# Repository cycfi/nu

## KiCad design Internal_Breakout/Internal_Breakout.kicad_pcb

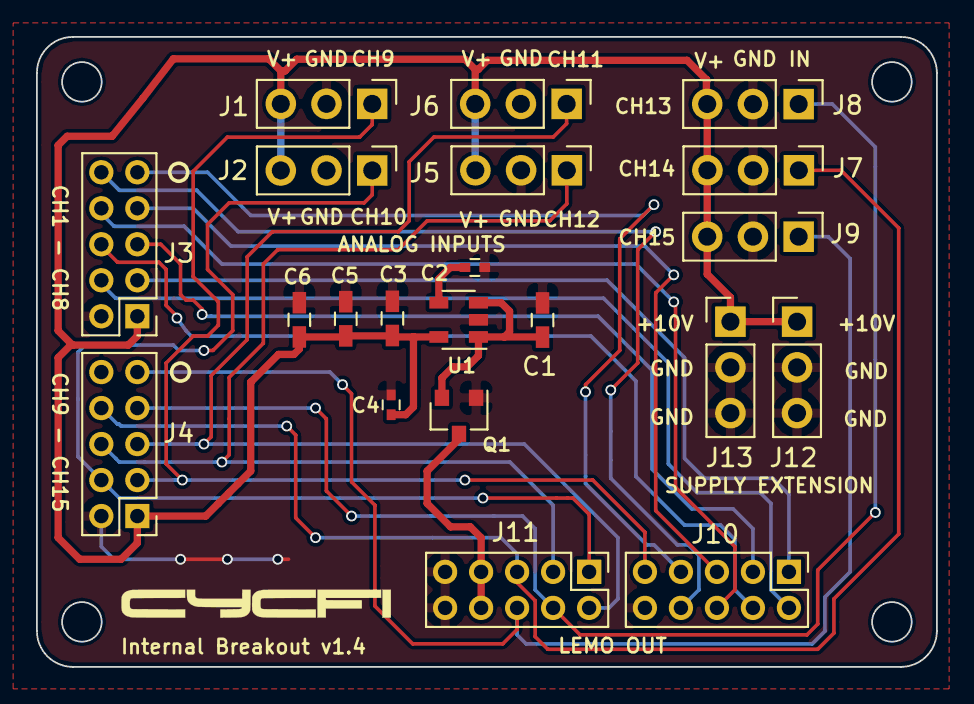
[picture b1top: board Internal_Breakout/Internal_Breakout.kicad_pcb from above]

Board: 2 copper layers, 50.0 x 35.0 mm, 21 parts (0 on the bottom side), 20 nets.

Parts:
C1, C5: 1uF; C_0603_HandSoldering
C2: 10nF; C_0402
C3: 2.2uF; C_0603_HandSoldering
C4: 1nF; C_0402
C6: 10uF; C_0603_HandSoldering
J1, J2, J5, J6, J7, J8, J9, J12, J13: CONN_01X03; Pin_Header_Straight_1x03_Pitch2.54mm
J3, J4, J10, J11: CONN_01X10; Pin_Header_Straight_2x05_Pitch2.00mm
Q1: DMP3099L-7; SOT-23
U1: LP2985-10DVBR; SOT-23-5

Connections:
+10VA: C3.1, C4.1, C5.1, C6.1, J1.3, J2.3, J3.1, J4.1, J5.3, J6.3, J7.3, J8.3, J9.3, J12.1, J13.1, U1.5
+VDC_IN: J11.7, J11.8, Q1.3
CH1: J3.3, J10.1
CH2: J3.4, J10.2
CH3: J3.5, J10.3
CH4: J3.6, J10.4
CH5: J3.7, J10.5
CH6: J3.8, J10.6
CH7: J3.9, J10.7
CH8: J3.10, J10.8
CH9: J1.1, J4.3, J10.9
CH10: J2.1, J4.4, J11.1
CH11: J4.5, J6.1, J11.2
CH12: J4.6, J5.1, J11.3
CH13: J4.7, J8.1, J11.4
CH14: J4.8, J7.1, J11.5
CH15: J4.9, J9.1, J11.6
GND: C1.2, C2.2, C3.2, C4.2, C5.2, C6.2, J1.2, J2.2, J3.2, J4.2, J5.2, J6.2, J7.2, J8.2, J9.2, J10.10, J11.9, J11.10, J12.2, J12.3, J13.2, J13.3, Q1.1, U1.2
unnamed: C1.1, Q1.2, U1.1, U1.3
unnamed: C2.1, U1.4

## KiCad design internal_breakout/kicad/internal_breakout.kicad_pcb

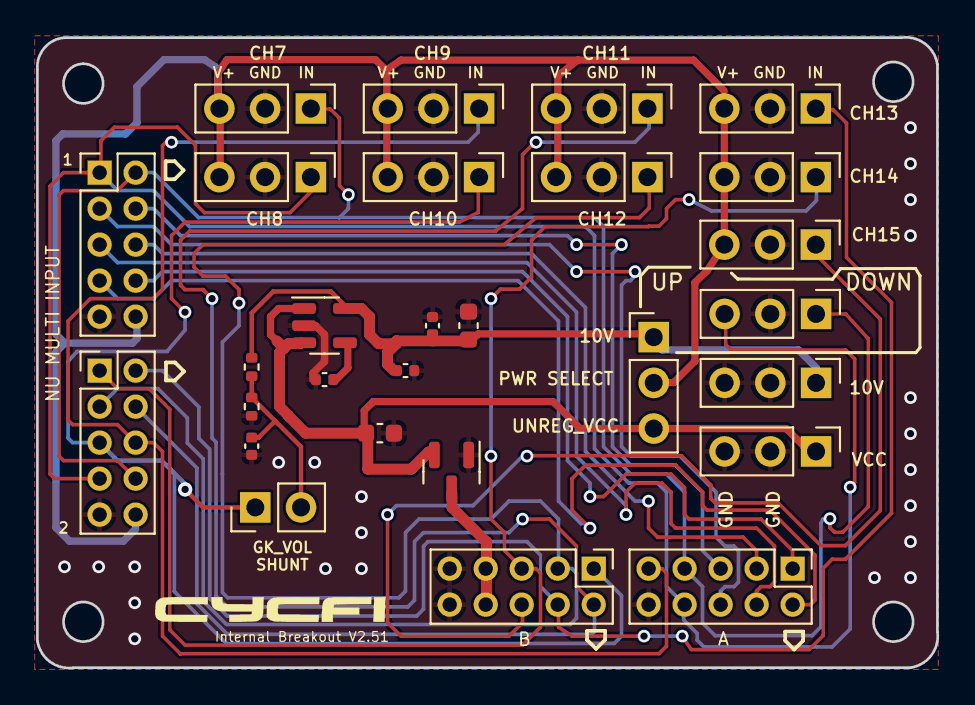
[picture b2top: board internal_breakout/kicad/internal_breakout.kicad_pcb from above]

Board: 2 copper layers, 50.0 x 35.0 mm, 28 parts (0 on the bottom side), 22 nets.

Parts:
C1, C2: 10uF; C_0603_1608Metric
C3, C6: 1uF; C_0402_1005Metric
C4: 10nF; C_0402_1005Metric
C5: 100nF; C_0402_1005Metric
J1, J2, J5, J6, J7, J8, J9, J12, J13, J14: MA03-1; PinHeader_1x03_P2.54mm_Vertical
J3, J4, J10, J11: 2X5; PinHeader_2x05_P2.00mm_Vertical
J15, J16, J17: Conn_01x03; PinHeader_1x03_P2.54mm_Vertical
J18: Conn_02x01; PinHeader_1x02_P2.54mm_Vertical
Q1: DMP3099L-7; SOT-23
R1, R2: 47K; R_0402_1005Metric
U1: LP2985-10DBVR; SOT-23-5

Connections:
+10VA: C2.1, C3.1, C5.1, J12.1, J14.1, R1.1, U1.5 (VOUT)
CH1: J3.8, J10.1
CH2: J3.7, J10.2
CH3: J3.6, J10.3
CH4: J3.5, J10.4
CH5: J3.4, J10.5
CH6: J3.3, J10.6
CH7: J3.2, J4.8, J10.7, J15.1, J17.1
CH8: J3.1, J4.7, J10.8, J16.1, J17.3
CH9: J1.1, J4.6, J10.9
CH10: J2.1, J4.5, J11.1, J18.1
CH11: J4.4, J6.1, J11.2
CH12: J4.3, J5.1, J11.3
CH13: J4.2, J8.1, J11.4
CH14: J4.1, J7.1, J11.5
CH15: J9.1, J11.6
GND: C1.2, C2.2, C3.2, C4.2, C5.2, C6.2, J1.2, J2.2, J3.9, J4.9, J5.2, J6.2, J7.2, J8.2, J9.2, J10.10, J11.9, J11.10, J12.2, J12.3, J13.2, J13.3, J15.2, J16.2, J17.2, Q1.1 (G), R2.2, U1.2 (GND)
unnamed: C4.1, U1.4 (BYPASS)
unnamed: C6.1, J18.2, R1.2, R2.1
V+: J1.3, J2.3, J3.10, J4.10, J5.3, J6.3, J7.3, J8.3, J9.3, J14.2, J15.3, J16.3
VCC: C1.1, J13.1, J14.3, Q1.2 (S), U1.1 (VIN), U1.3 (ON/OFF)
VIN: J11.7, J11.8, Q1.3 (D)

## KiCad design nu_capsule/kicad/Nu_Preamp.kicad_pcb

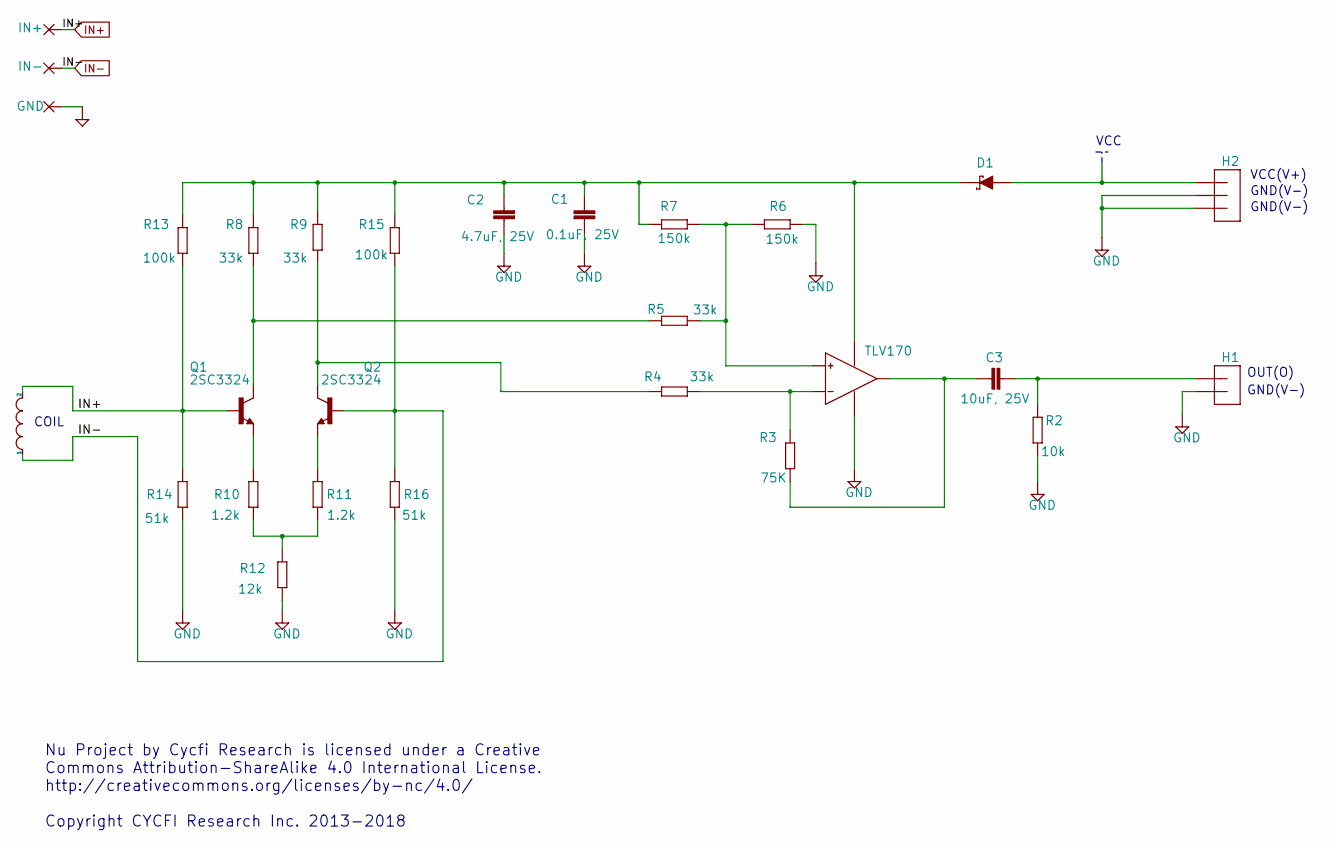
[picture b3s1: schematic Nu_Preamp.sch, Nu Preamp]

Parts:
C1: 0.1uF, 25V; C0402
C2: 4.7uF, 25V; C0603_NK
C3: 10uF, 25V; C0603_NK
D1: SOD323
GND: SMD1_27-2_54
H1: 2P-2MM-TH-MALE; 2P-2MM-TH
H2: 3P-2MM-TH-MALE; 3P-2MM-TH
IN+: SMD1_27-2_54
IN-: SMD1_27-2_54
Q1, Q2: 2SC3324; SOT23
R2: 10k; R0402
R3: 75K; R0402
R4, R5, R8, R9: 33k; R0402
R6, R7: 150k; R0402
R10, R11: 1.2k; R0402
R12: 12k; R0402
R13, R15: 100k; R0402
R14, R16: 51k; R0402
U1: TLV170; SOT23-5

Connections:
GND: C1.2, C2.1, GND.1, H1.P$2 (2), H2.P$2 (2), H2.P$3 (3), R2.1, R6.1, R12.1, R14.1, R16.1, U1.2
IN+: IN+.1, Q1.1 (B), R13.1, R14.2
IN-: IN-.1, Q2.1 (B), R15.1, R16.2
unnamed: C3.2, H1.P$1 (1), R2.2
unnamed: Q1.3 (C), R5.2, R8.1
unnamed: Q2.3 (C), R4.2, R9.1
unnamed: Q1.2 (E), R10.2
unnamed: Q2.2 (E), R11.2
unnamed: R10.1, R11.1, R12.2
unnamed: R5.1, R6.2, R7.1, U1.3
unnamed: R3.1, R4.1, U1.4
unnamed: C3.1, R3.2, U1.1
unnamed: D1.1 (A), H2.P$1 (1)
VCC1: C1.1, C2.2, D1.2 (C), R7.2, R8.2, R9.2, R13.2, R15.2, U1.5

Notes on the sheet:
Nu Project by Cycfi Research is licensed under a Creative Commons Attribution-ShareAlike 4.0 International License. http://creativecommons.org/licenses/by-nc/4.0/ Copyright CYCFI Research Inc. 2013-2018
VCC
COIL
VCC(V+)
GND(V-)
OUT(O)

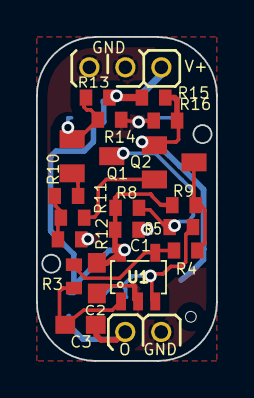
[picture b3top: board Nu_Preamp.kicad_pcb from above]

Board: 2 copper layers, 10.0 x 18.0 mm, 28 parts (0 on the bottom side), 14 nets.

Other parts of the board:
@HOLE0: (no value)

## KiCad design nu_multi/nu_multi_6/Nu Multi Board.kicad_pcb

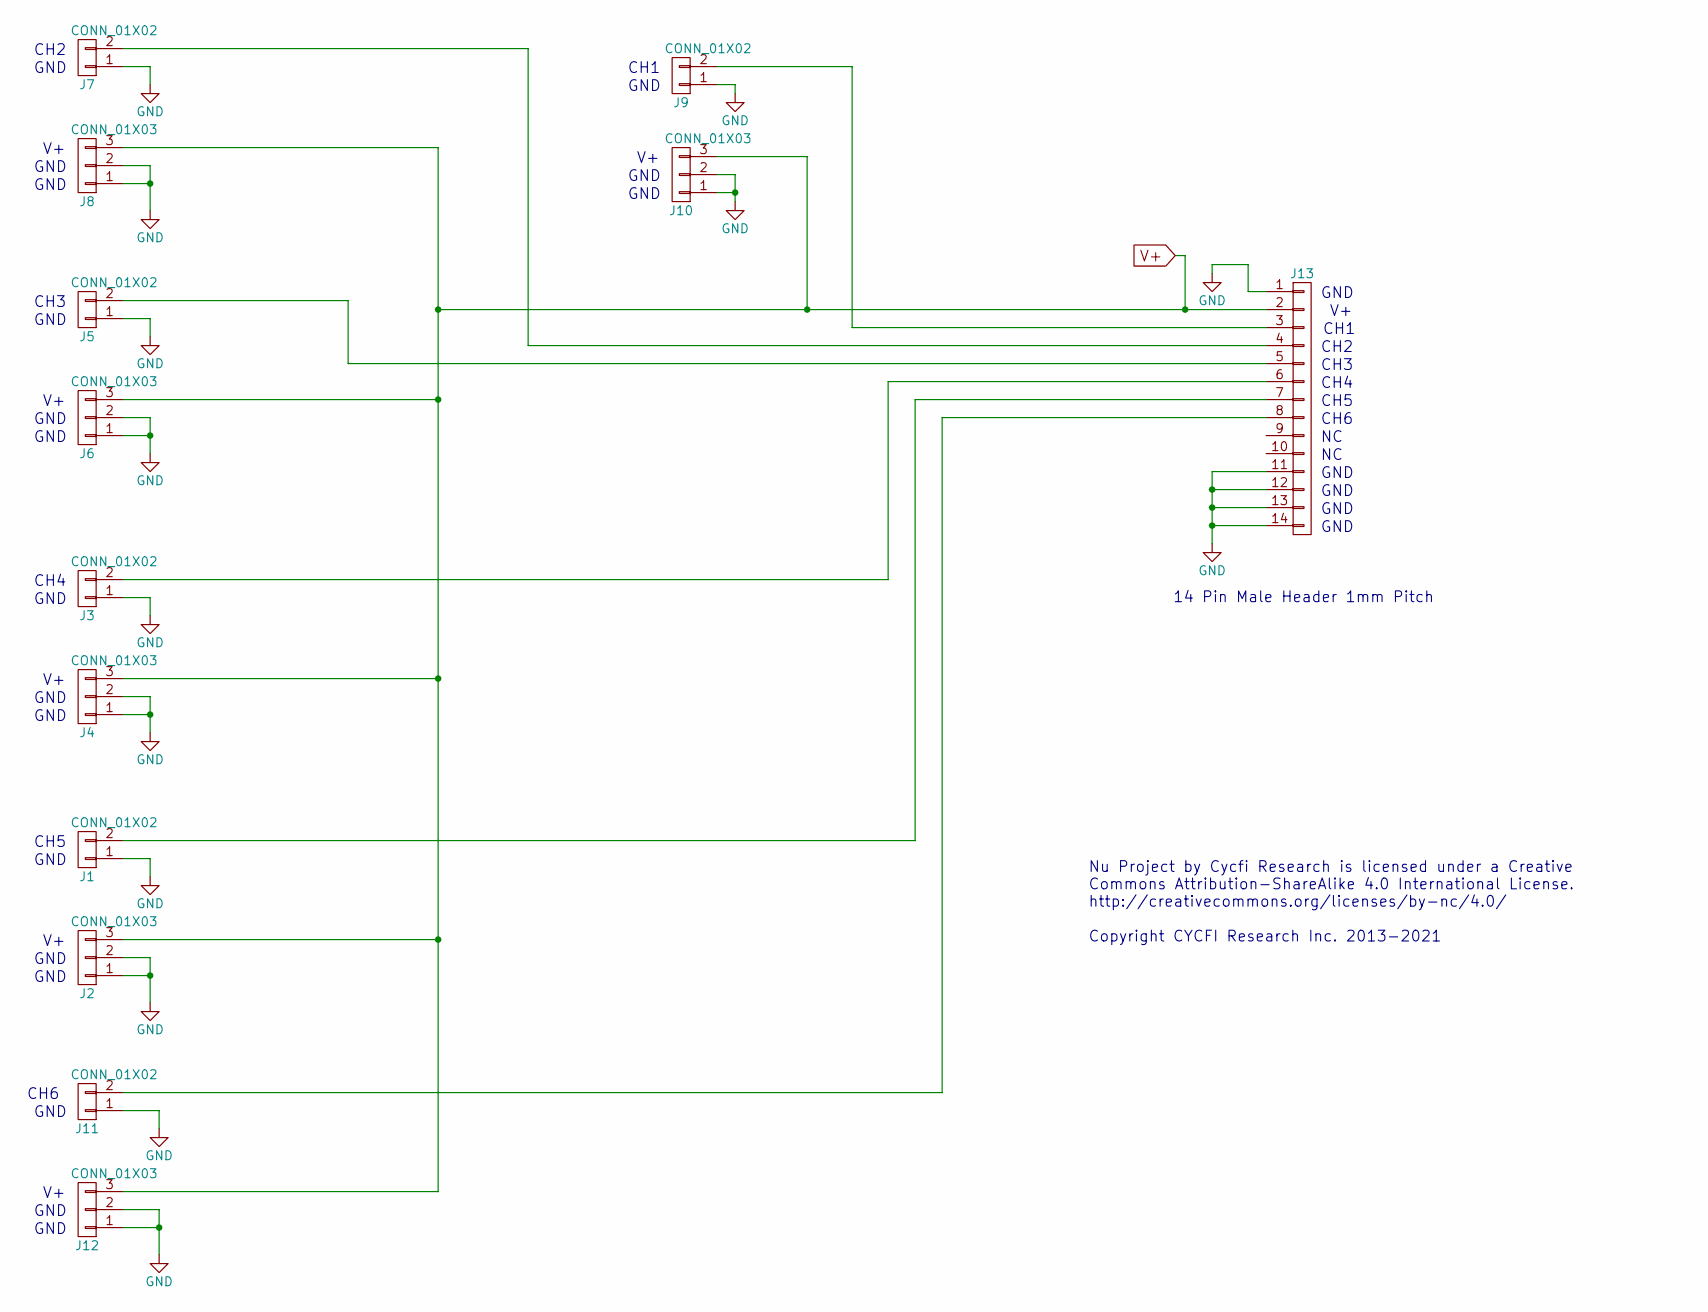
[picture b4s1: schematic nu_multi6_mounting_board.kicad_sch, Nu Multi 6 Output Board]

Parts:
J1, J3, J5, J7, J9, J11: CONN_01X02; Pin_Header_Straight_1x02_Pitch2.00mm
J2, J4, J6, J8, J10, J12: CONN_01X03; Pin_Header_Straight_1x03_Pitch2.00mm
J13: CONN_01X14; Pin_Header_Straight_2x07_Pitch1.00mm_SMD

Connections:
GND: J1.1, J2.1, J2.2, J3.1, J4.1, J4.2, J5.1, J6.1, J6.2, J7.1, J8.1, J8.2, J9.1, J10.1, J10.2, J11.1, J12.1, J12.2, J13.1, J13.11, J13.12, J13.13, J13.14
unnamed: J1.2, J13.7
unnamed: J11.2, J13.8
unnamed: J9.2, J13.3
unnamed: J7.2, J13.4
unnamed: J5.2, J13.5
unnamed: J3.2, J13.6
V+: J2.3, J4.3, J6.3, J8.3, J10.3, J12.3, J13.2

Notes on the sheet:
GND
CH1
CH4
CH5
14 Pin Male Header 1mm Pitch
CH2
CH3
CH6
CH2
CH6
CH1
Nu Project by Cycfi Research is licensed under a Creative Commons Attribution-ShareAlike 4.0 International License. http://creativecommons.org/licenses/by-nc/4.0/ Copyright CYCFI Research Inc. 2013-2021

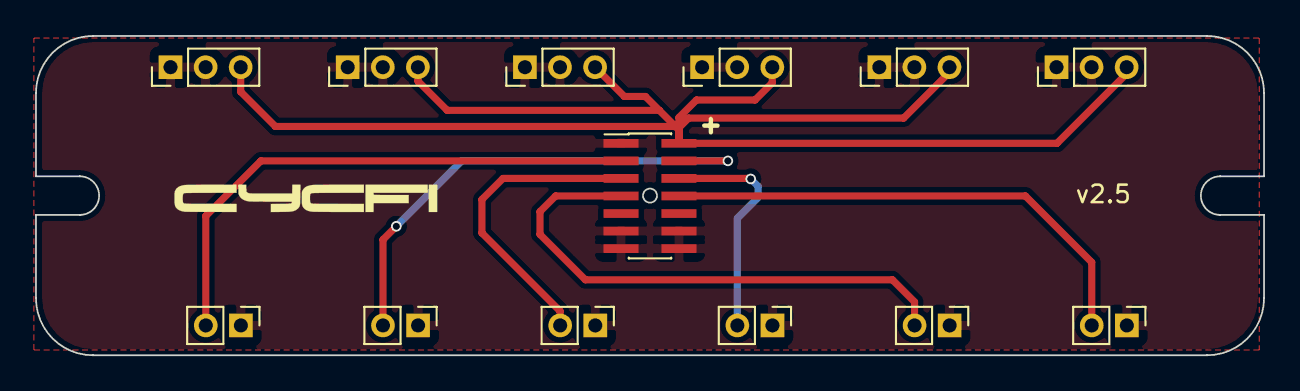
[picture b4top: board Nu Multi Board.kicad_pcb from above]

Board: 2 copper layers, 70.0 x 18.2 mm, 13 parts (0 on the bottom side), 8 nets.

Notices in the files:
nu_capsule/kicad/modified_eagle_files/Nu_Preamp.sch:
Copyright CYCFI Research Inc. 2013-2017
